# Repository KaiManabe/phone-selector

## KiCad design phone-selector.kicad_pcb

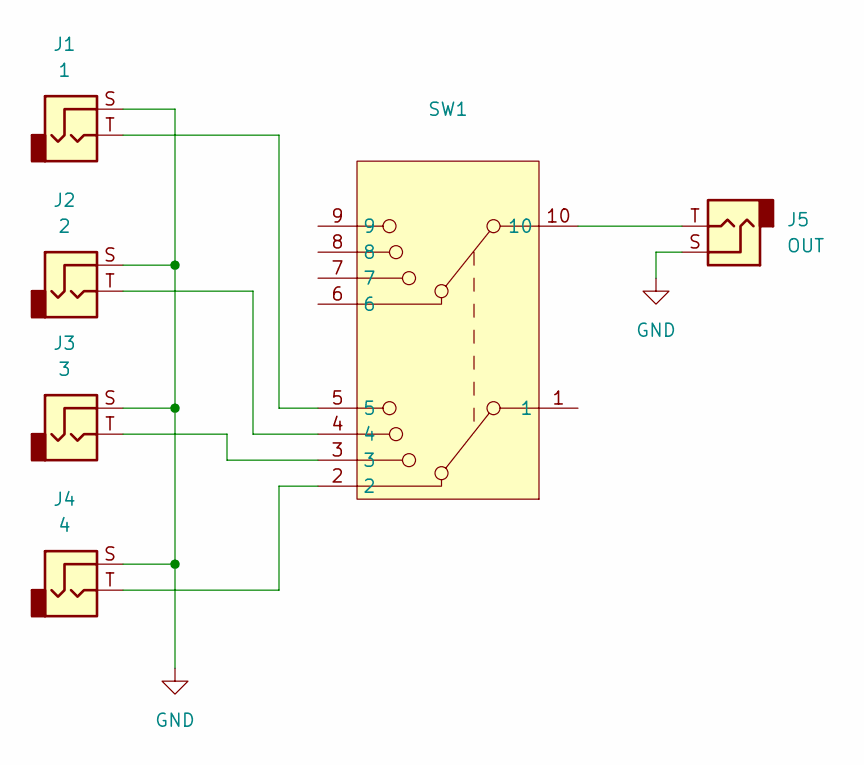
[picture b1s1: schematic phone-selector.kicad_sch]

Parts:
J1: 1; MJ-188LPD-8C
J2: 2; MJ-188LPD-8C
J3: 3; MJ-188LPD-8C
J4: 4; MJ-188LPD-8C
J5: OUT; MJ-188LPD-8C
SW1: SR1712F-0204-15K0A-B9-N-027

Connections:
GND: J1.S, J2.S, J3.S, J4.S, J5.S
unnamed: J1.T, SW1.5
unnamed: J2.T, SW1.4
unnamed: J3.T, SW1.3
unnamed: J4.T, SW1.2
unnamed: J5.T, SW1.10

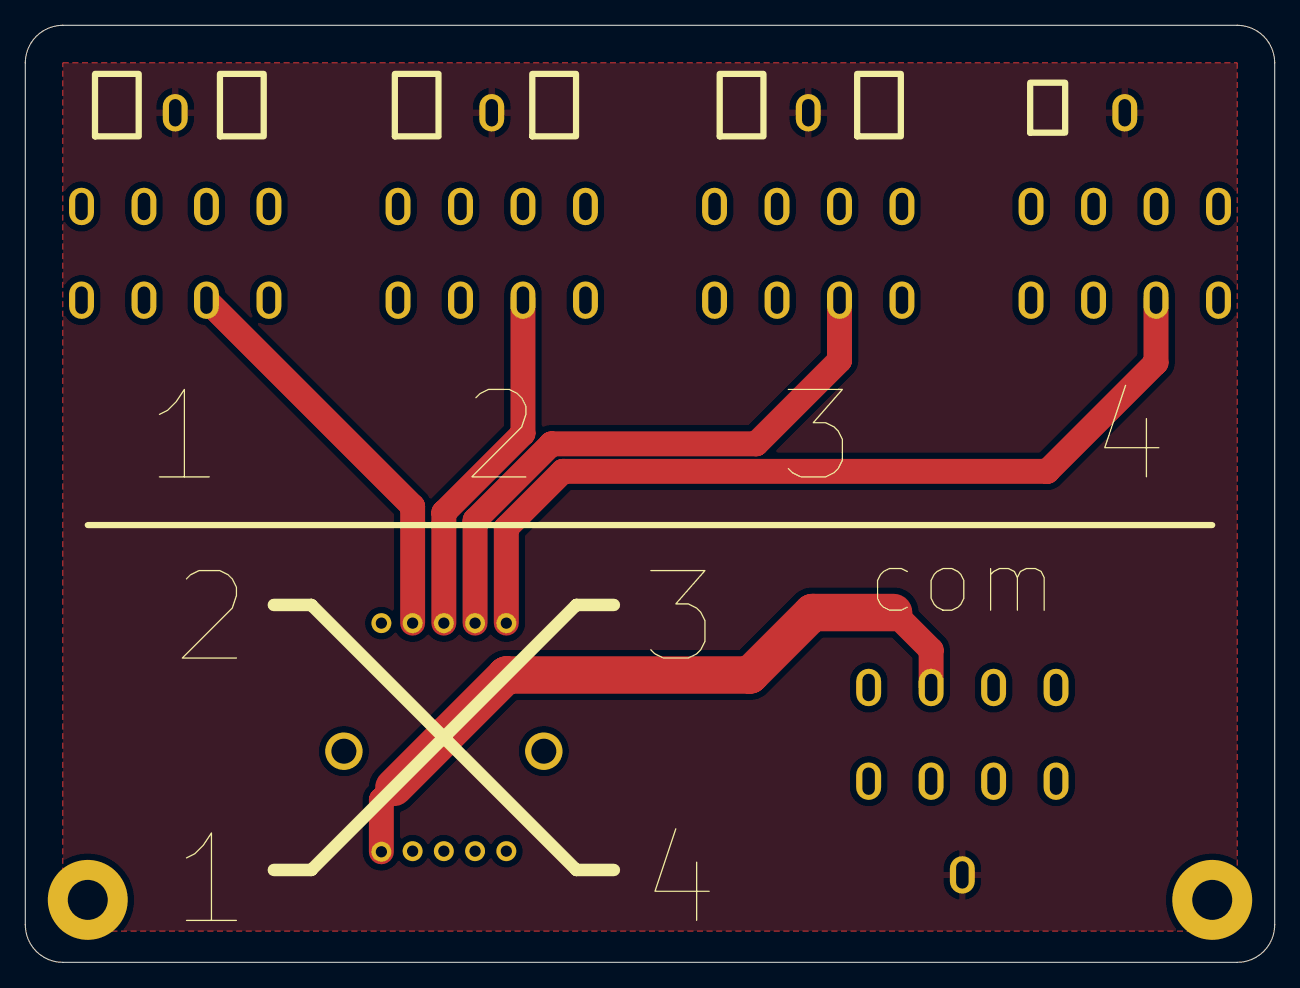
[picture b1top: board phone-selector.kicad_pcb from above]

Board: 2 copper layers, 100.0 x 75.0 mm, 6 parts (0 on the bottom side), 6 nets.

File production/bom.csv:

Designator,Footprint,Quantity,Value,LCSC Part #
J1,MJ-188LPD-8C,1,1,
J2,MJ-188LPD-8C,1,2,
J3,MJ-188LPD-8C,1,3,
J4,MJ-188LPD-8C,1,4,
J5,MJ-188LPD-8C,1,OUT,
SW1,SR1712F-0204-15K0A-B9-N-027,1,~,

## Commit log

2026-04-10 Add prototype
